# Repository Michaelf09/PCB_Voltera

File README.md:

# Tiltis Key - PCB KiCad

Projet KiCad réalisé dans le cadre du projet PI² de l’ESILV.
Conception du PCB de la Tiltis Key avec fabrication prévue sur imprimante Voltera.

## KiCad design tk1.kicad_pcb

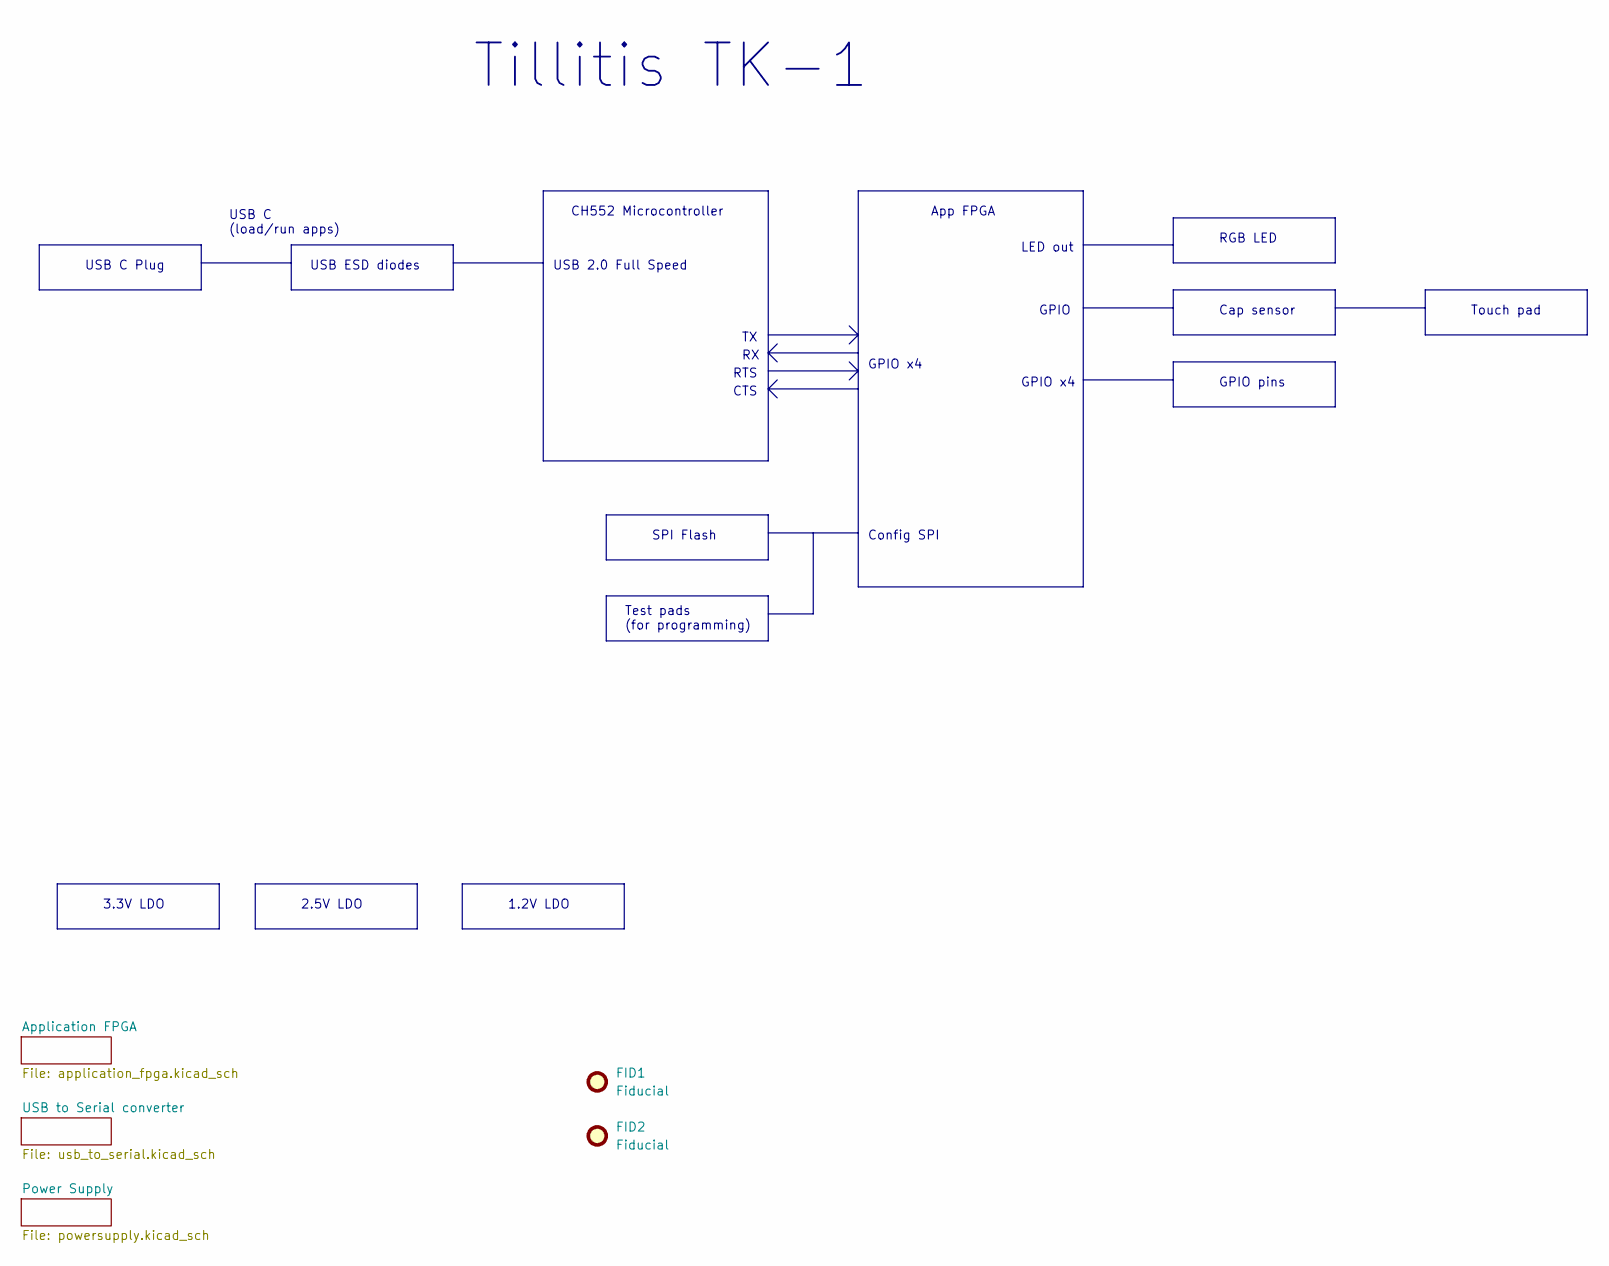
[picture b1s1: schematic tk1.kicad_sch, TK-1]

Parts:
FID1, FID2: Fiducial; Fiducial_0.75mm_Mask1.5mm

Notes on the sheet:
USB ESD diodes
Touch pad
GPIO x4
GPIO pins
Cap sensor
USB 2.0 Full Speed
RTS
USB C Plug
CH552 Microcontroller
RGB LED
USB C (load/run apps)
1.2V LDO
3.3V LDO
CTS
2.5V LDO
App FPGA
Config SPI
Tillitis TK-1
SPI Flash
GPIO
LED out
Test pads (for programming)

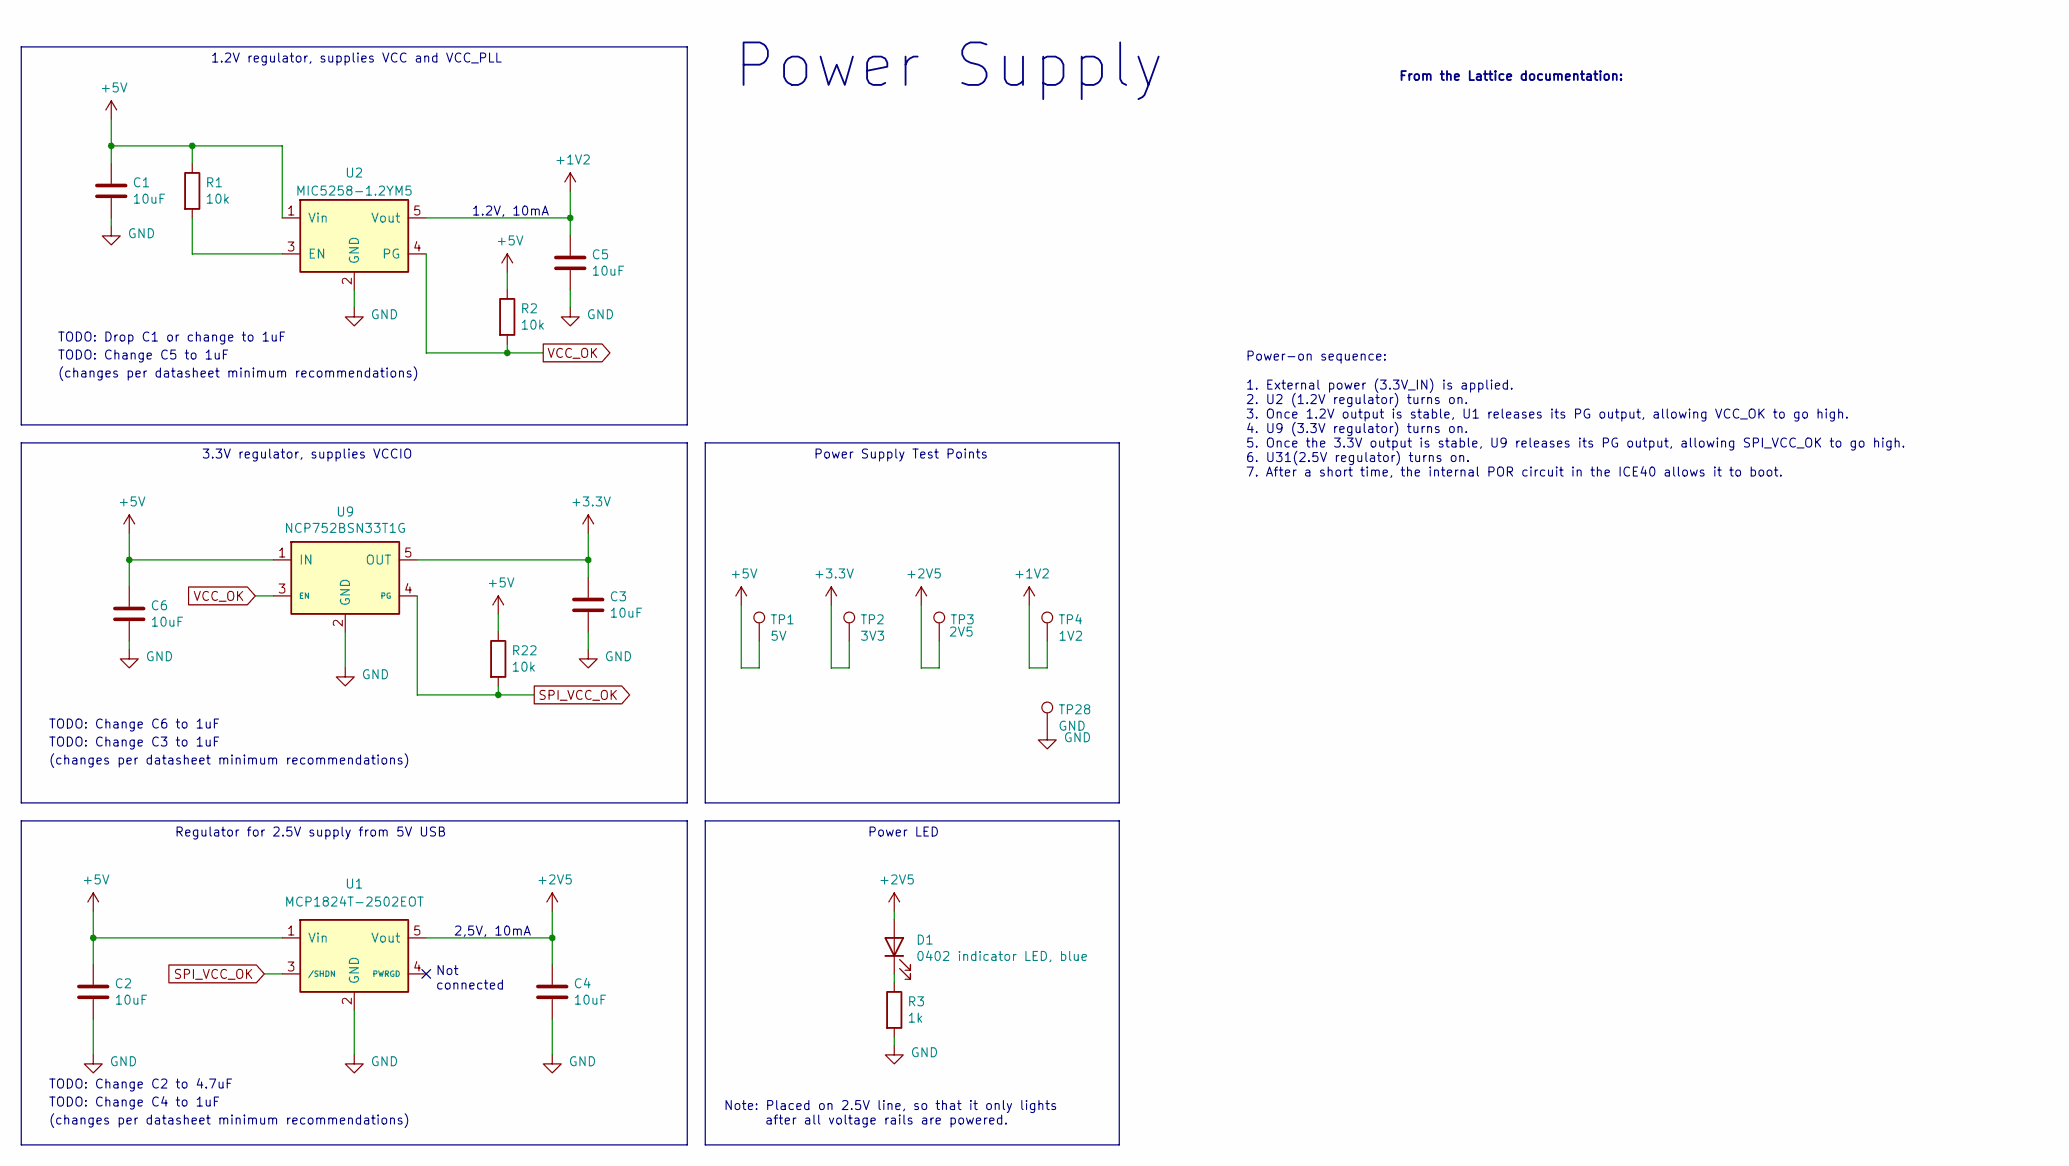
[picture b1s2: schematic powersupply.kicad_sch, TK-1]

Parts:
C1, C2, C3, C4, C5, C6: 10uF; C_0805_2012Metric
D1: 0402 indicator LED, blue; LED_0805_2012Metric; Manufacturer Part Number NCD0402B1
R1, R2, R22: 10k; R_0805_2012Metric
R3: 1k; R_0805_2012Metric
TP1: 5V; TestPoint_Pad_D1.0mm
TP2: 3V3; TestPoint_Pad_D1.0mm
TP3: 2V5; TestPoint_Pad_D1.0mm
TP4: 1V2; TestPoint_Pad_D1.0mm
TP28: GND; TestPoint_Pad_D1.0mm
U1: MCP1824T-2502EOT; SOT-23-5; Manufacturer Part Number MCP1824T-2502EOT
U2: MIC5258-1.2YM5; SOT-23-5; Manufacturer Part Number MIC5258-1.2YM5
U9: NCP752BSN33T1G; Manufacturer Part Number NCP752BSN33T1G

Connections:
+1V2: C5.1, TP4.1, U2.5 (Vout); also elsewhere on the board
+2V5: C4.1, D1.2 (A), TP3.1, U1.5 (Vout); also elsewhere on the board
+3.3V: C3.1, TP2.1, U9.5 (OUT); also elsewhere on the board
+5V: C1.1, C2.1, C6.1, R1.1, R2.1, R22.1, TP1.1, U1.1 (Vin), U2.1 (Vin), U9.1 (IN); also elsewhere on the board
GND: C1.2, C2.2, C3.2, C4.2, C5.2, C6.2, R3.2, TP28.1, U1.2 (GND), U2.2 (GND), U9.2 (GND); also elsewhere on the board
unnamed: D1.1 (K), R3.1
unnamed: R1.2, U2.3 (EN)
SPI_VCC_OK: R22.2, U1.3 (/SHDN), U9.4 (PG)
VCC_OK: R2.2, U2.4 (PG), U9.3 (EN)

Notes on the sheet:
Power-on sequence: 1. External power (3.3V_IN) is applied. 2. U2 (1.2V regulator) turns on. 3. Once 1.2V output is stable, U1 releases its PG output, allowing VCC_OK to go high. 4. U9 (3.3V regulator) turns on. 5. Once the 3.3V output is stable, U9 releases its PG output, allowing SPI_VCC_OK to go 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
TODO: Change C2 to 4.7uF
(changes per datasheet minimum recommendations)
TODO: Change C6 to 1uF
2,5V, 10mA
Note: Placed on 2.5V line, so that it only lights after all voltage rails are powered.
TODO: Change C3 to 1uF
1.2V, 10mA
Power Supply
TODO: Drop C1 or change to 1uF
TODO: Change C5 to 1uF
From the Lattice documentation:
1.2V regulator, supplies VCC and VCC_PLL
3.3V regulator, supplies VCCIO
TODO: Change C4 to 1uF
Not connected
Power Supply Test Points
Power LED
Regulator for 2.5V supply from 5V USB

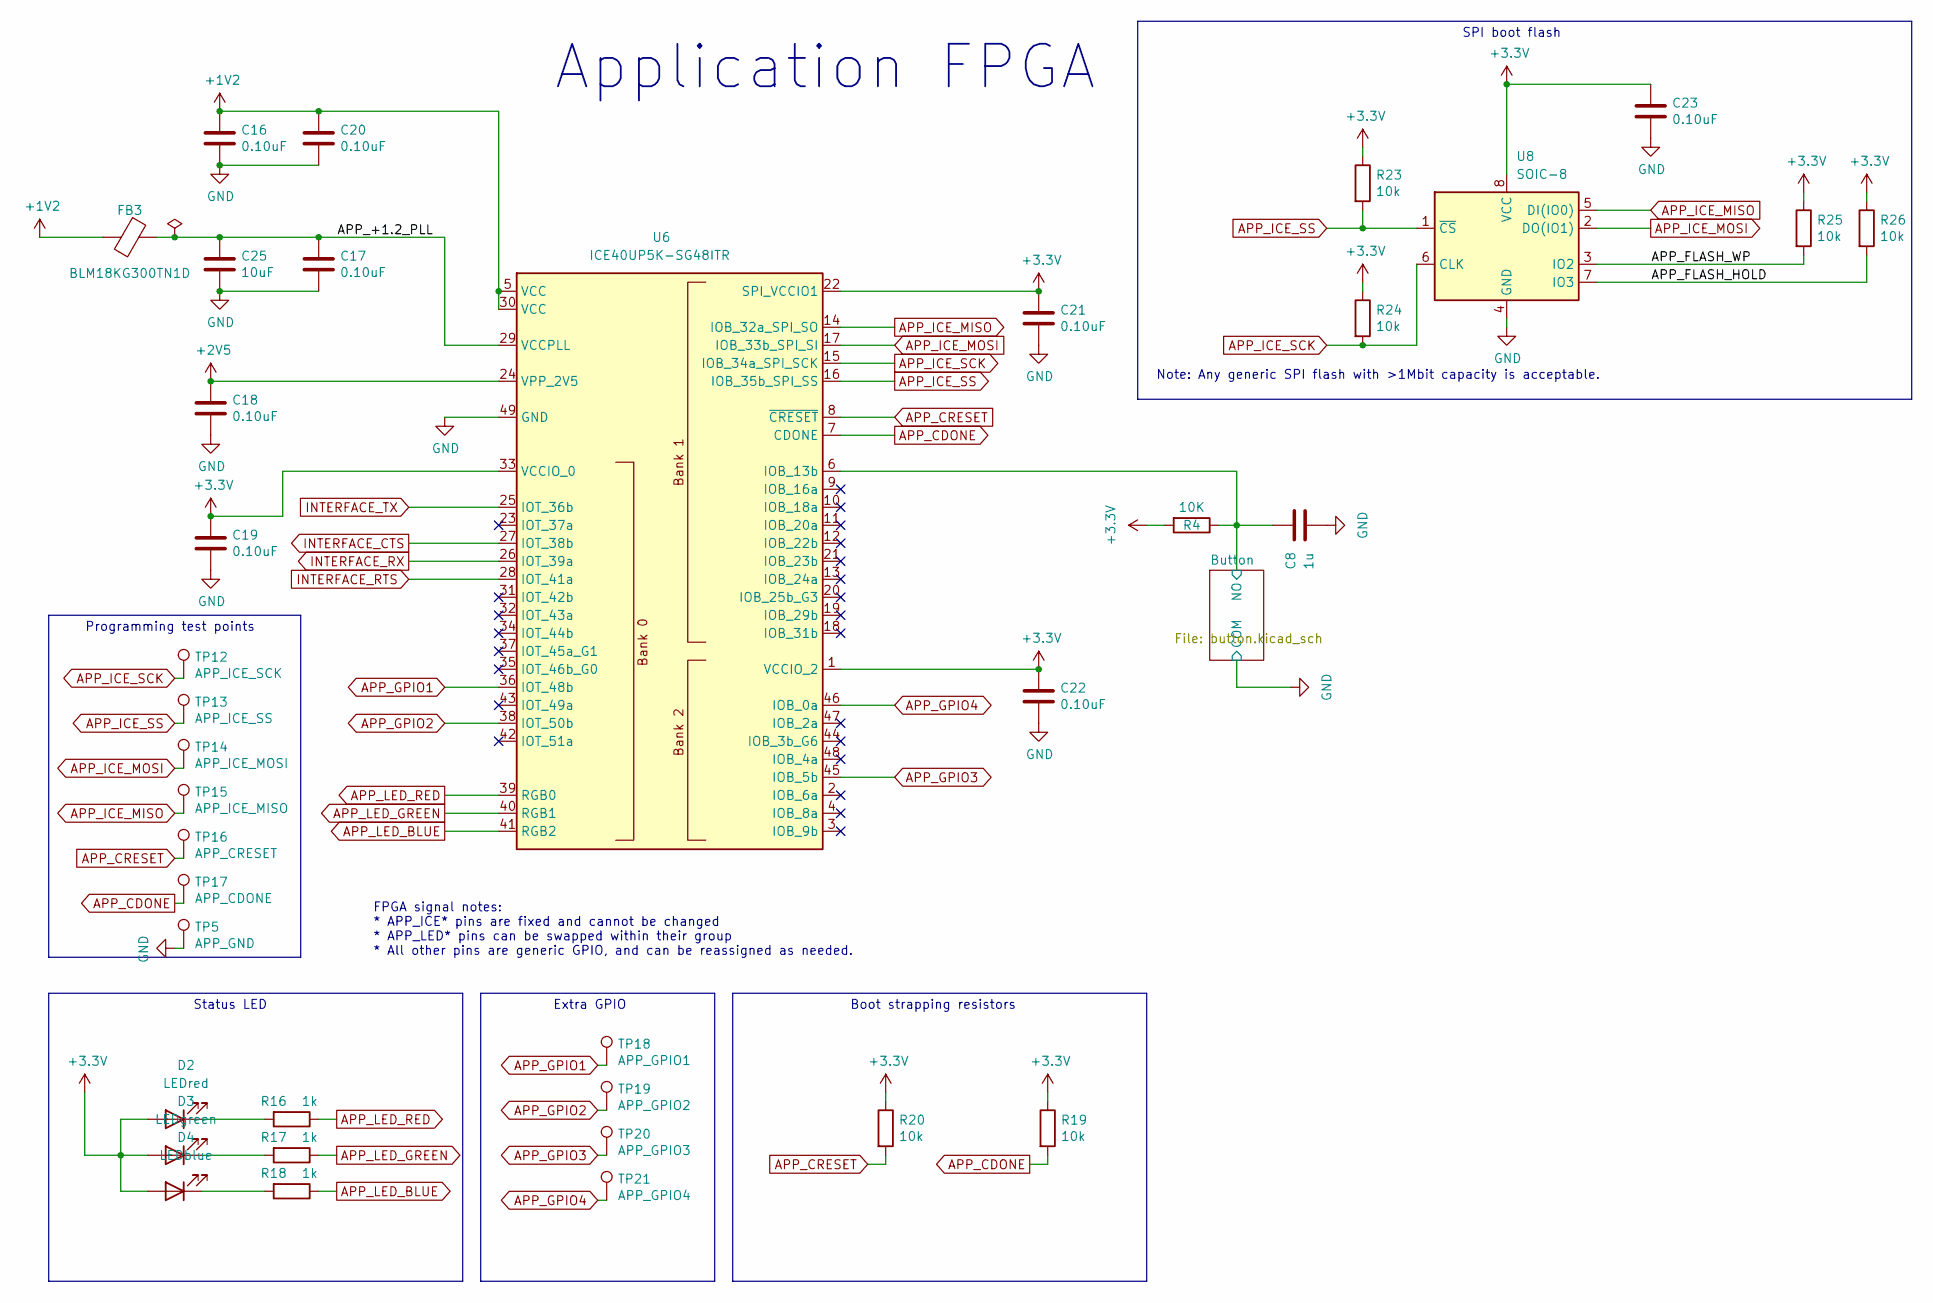
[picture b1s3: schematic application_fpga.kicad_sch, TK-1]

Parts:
C8: 1u; C_0805_2012Metric_Pad1.18x1.45mm_HandSolder
C16, C17, C18, C19, C20, C21, C22, C23: 0.10uF; C_0805_2012Metric
C25: 10uF; C_0805_2012Metric
D2: LEDred; LED_0805_2012Metric_Pad1.15x1.40mm_HandSolder
D3: LEDgreen; LED_0805_2012Metric_Pad1.15x1.40mm_HandSolder
D4: LEDblue; LED_0805_2012Metric_Pad1.15x1.40mm_HandSolder
FB3: BLM18KG300TN1D; Ferritbead_0603_1608Metric; Manufacturer Part Number BLM18KG300TN1D
R4: 10K; R_0805_2012Metric_Pad1.20x1.40mm_HandSolder
R16, R17, R18: 1k; R_0805_2012Metric
R19, R20, R23, R24, R25, R26: 10k; R_0805_2012Metric
TP5: APP_GND; TestPoint_Pad_D1.0mm
TP12: APP_ICE_SCK; TestPoint_Pad_D1.0mm
TP13: APP_ICE_SS; TestPoint_Pad_D1.0mm
TP14: APP_ICE_MOSI; TestPoint_Pad_D1.0mm
TP15: APP_ICE_MISO; TestPoint_Pad_D1.0mm
TP16: APP_CRESET; TestPoint_Pad_D1.0mm
TP17: APP_CDONE; TestPoint_Pad_D1.0mm
TP18: APP_GPIO1; TestPoint_Pad_D1.0mm
TP19: APP_GPIO2; TestPoint_Pad_D1.0mm
TP20: APP_GPIO3; TestPoint_Pad_D1.0mm
TP21: APP_GPIO4; TestPoint_Pad_D1.0mm
U6: ICE40UP5K-SG48ITR; QFN-48-1EP_7x7mm_P0.5mm_EP5.6x5.6mm; Manufacturer Part Number ICE40UP5K-SG48ITR
U8: SOIC-8; SOIC-8_3.9x4.9mm_P1.27mm; Manufacturer Part Number W25Q80DVUXIE

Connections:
+1V2: C16.1, C20.1, FB3.2, U6.5 (VCC), U6.30 (VCC); also elsewhere on the board
+2V5: C18.1, U6.24 (VPP_2V5); also elsewhere on the board
+3.3V: C19.1, C21.1, C22.1, C23.1, D2.2 (A), D3.2 (A), D4.2 (A), R4.2, R19.1, R20.1, R23.1, R24.1, R25.1, R26.1, U6.1 (VCCIO_2), U6.22 (SPI_VCCIO1), U6.33 (VCCIO_0), U8.8 (VCC); also elsewhere on the board
/Application FPGA/APP_+1.2_PLL: C17.1, C25.1, FB3.1, U6.29 (VCCPLL)
/Application FPGA/APP_FLASH_HOLD: R26.2, U8.7 (IO3)
/Application FPGA/APP_FLASH_WP: R25.2, U8.3 (IO2)
/Application FPGA/Button/NO: C8.1, R4.1, U6.6 (IOB_13b); also elsewhere on the board
APP_CDONE: R19.2, TP17.1, U6.7 (CDONE)
APP_CRESET: R20.2, TP16.1, U6.8 (~CRESET)
APP_GPIO1: TP18.1, U6.36 (IOT_48b)
APP_GPIO2: TP19.1, U6.38 (IOT_50b)
APP_GPIO3: TP20.1, U6.45 (IOB_5b)
APP_GPIO4: TP21.1, U6.46 (IOB_0a)
APP_ICE_MISO: TP15.1, U6.14 (IOB_32a_SPI_SO), U8.5 (DI(IO0))
APP_ICE_MOSI: TP14.1, U6.17 (IOB_33b_SPI_SI), U8.2 (DO(IO1))
APP_ICE_SCK: R24.2, TP12.1, U6.15 (IOB_34a_SPI_SCK), U8.6 (CLK)
APP_ICE_SS: R23.2, TP13.1, U6.16 (IOB_35b_SPI_SS), U8.1 (~CS)
APP_LED_BLUE: R18.1, U6.41 (RGB2)
APP_LED_GREEN: R17.1, U6.40 (RGB1)
APP_LED_RED: R16.1, U6.39 (RGB0)
GND: C8.2, C16.2, C17.2, C18.2, C19.2, C20.2, C21.2, C22.2, C23.2, C25.2, TP5.1, U6.49 (GND), U8.4 (GND); also elsewhere on the board
INTERFACE_CTS: U6.27 (IOT_38b); also elsewhere on the board
INTERFACE_RTS: U6.28 (IOT_41a); also elsewhere on the board
INTERFACE_RX: U6.26 (IOT_39a); also elsewhere on the board
INTERFACE_TX: U6.25 (IOT_36b); also elsewhere on the board
unnamed: D2.1 (K), R16.2
unnamed: D3.1 (K), R17.2
unnamed: D4.1 (K), R18.2

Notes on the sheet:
Application FPGA
SPI boot flash
FPGA signal notes: * APP_ICE* pins are fixed and cannot be changed * APP_LED* pins can be swapped within their group * All other pins are generic GPIO, and can be reassigned as needed.
Boot strapping resistors
Status LED
Programming test points
Note: Any generic SPI flash with >1Mbit capacity is acceptable.
Extra GPIO

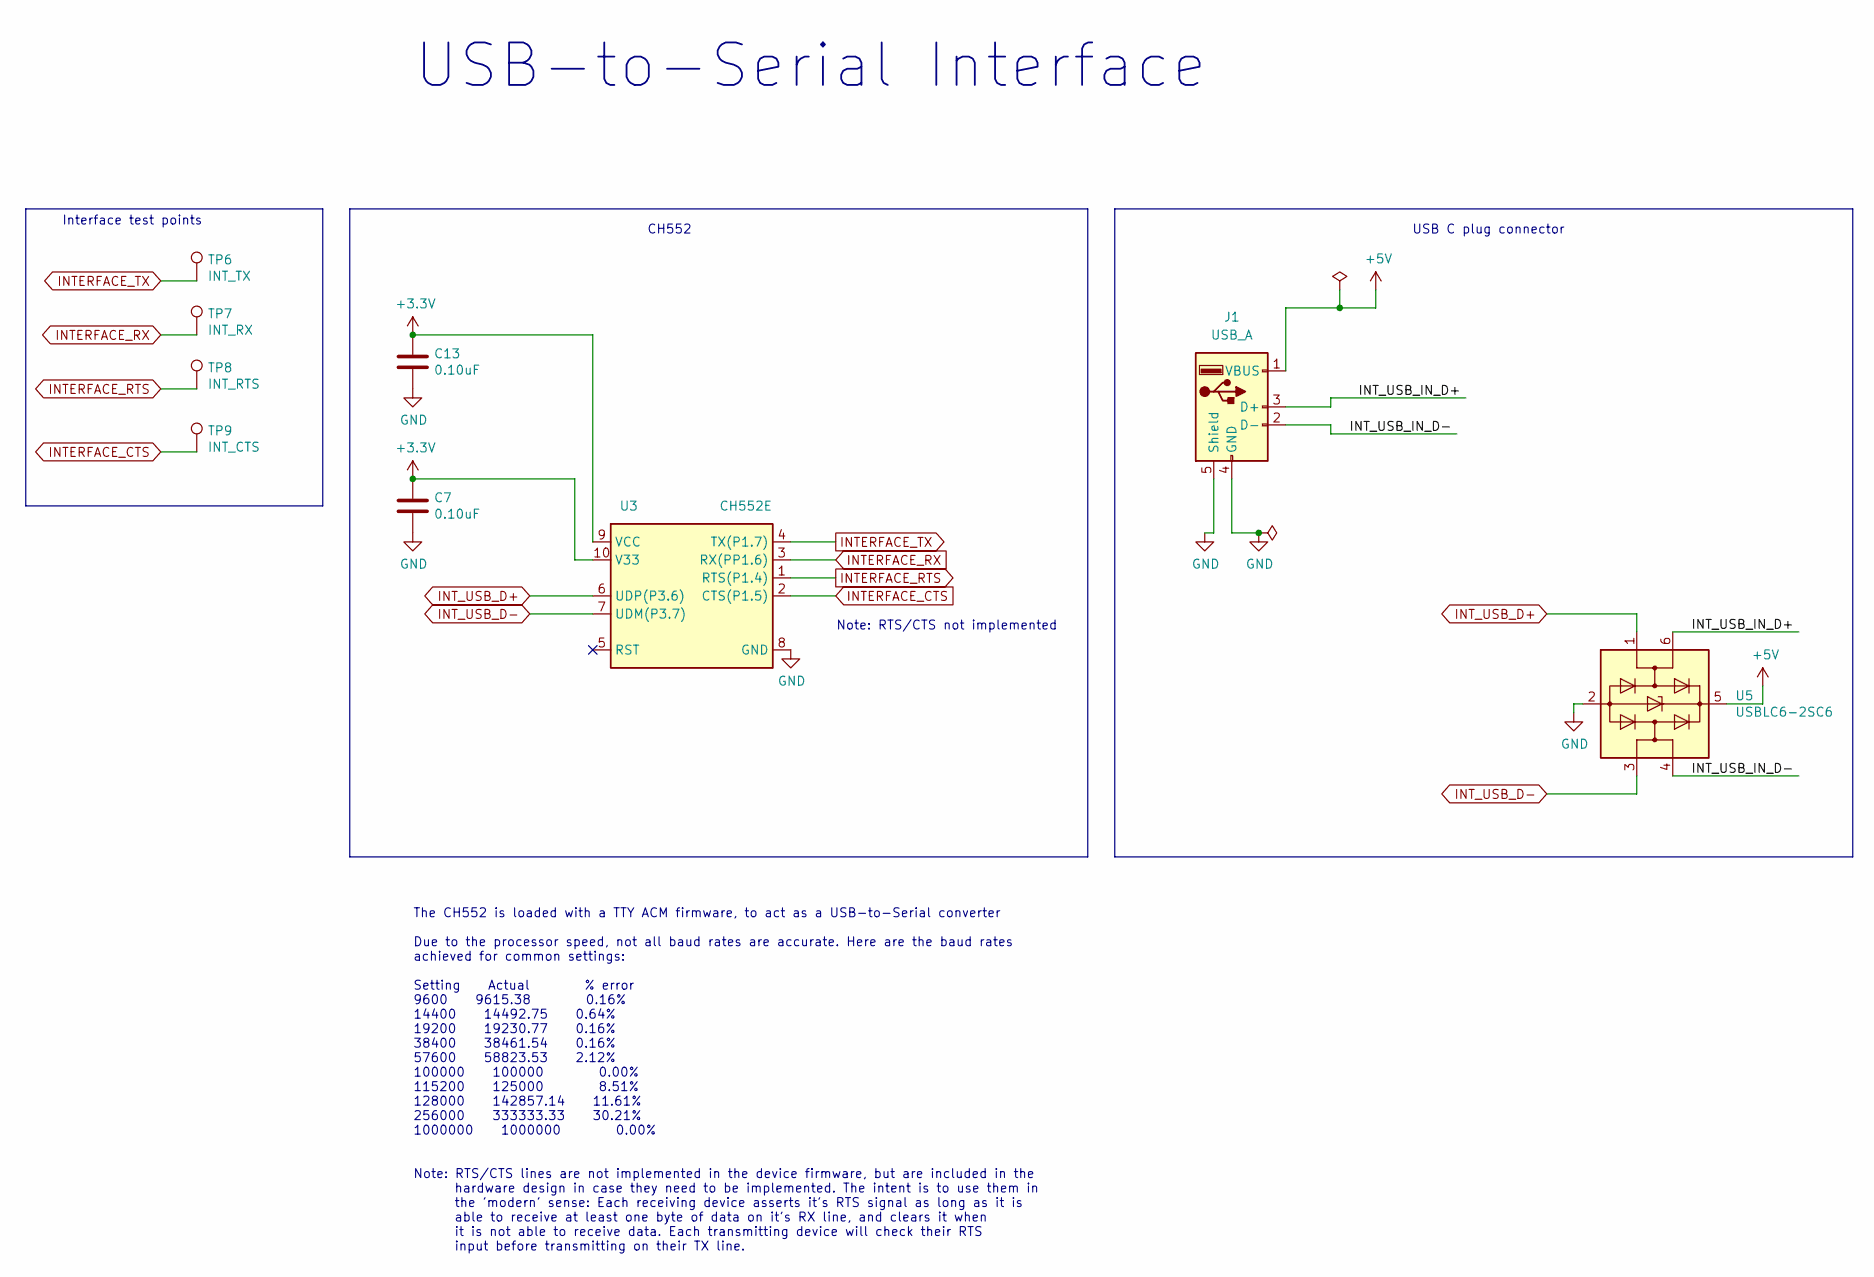
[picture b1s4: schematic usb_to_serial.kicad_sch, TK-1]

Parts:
C7, C13: 0.10uF; C_0805_2012Metric
J1: USB_A; USB_A_Kycon_KUSBX-AS1N-B_Horizontal
TP6: INT_TX; TestPoint_Pad_D1.0mm
TP7: INT_RX; TestPoint_Pad_D1.0mm
TP8: INT_RTS; TestPoint_Pad_D1.0mm
TP9: INT_CTS; TestPoint_Pad_D1.0mm
U3: CH552E; MSOP-10_3x3mm_P0.5mm; Manufacturer Part Number CH552E
U5: USBLC6-2SC6; SOT-23-6; Manufacturer Part Number USBLC6-2SC6

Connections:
+3.3V: C7.1, C13.1, U3.9 (VCC), U3.10 (V33); also elsewhere on the board
+5V: J1.1 (VBUS), U5.5 (VBUS); also elsewhere on the board
/USB to Serial converter/INT_USB_IN_D+: J1.3 (D+), U5.6 (I/O1)
/USB to Serial converter/INT_USB_IN_D-: J1.2 (D-), U5.4 (I/O2)
GND: C7.2, C13.2, J1.4 (GND), J1.5 (Shield), U3.8 (GND), U5.2 (GND); also elsewhere on the board
INTERFACE_CTS: TP9.1, U3.2 (CTS(P1.5)); also elsewhere on the board
INTERFACE_RTS: TP8.1, U3.1 (RTS(P1.4)); also elsewhere on the board
INTERFACE_RX: TP7.1, U3.3 (RX(PP1.6)); also elsewhere on the board
INTERFACE_TX: TP6.1, U3.4 (TX(P1.7)); also elsewhere on the board
INT_USB_D+: U3.6 (UDP(P3.6)), U5.1 (I/O1)
INT_USB_D-: U3.7 (UDM(P3.7)), U5.3 (I/O2)

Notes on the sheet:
USB C plug connector
CH552
USB-to-Serial Interface
The CH552 is loaded with a TTY ACM firmware, to act as a USB-to-Serial converter Due to the processor speed, not all baud rates are accurate. Here are the baud rates achieved for common settings: Setting Actual % error 9600 9615.38 0.16% 14400 14492.75 0.64% 19200 19230.77 0.16% 38400 38461.54 0.16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
Interface test points
Note: RTS/CTS not implemented

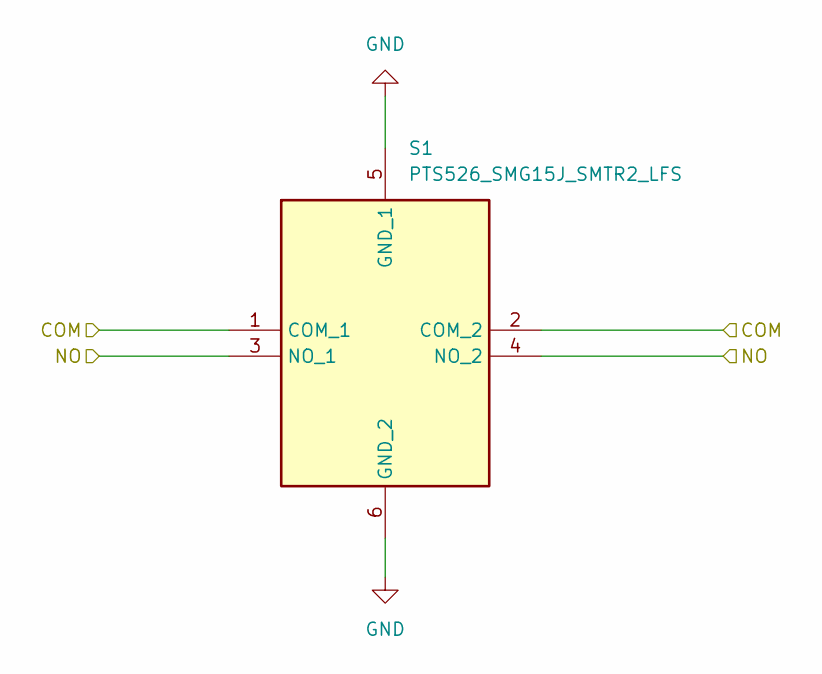
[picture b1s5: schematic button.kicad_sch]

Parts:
S1: PTS526_SMG15J_SMTR2_LFS; PTS526SMG15JSMTR2LFS; Manufacturer_Part_Number PTS526 SMG15J SMTR2 LFS; Mouser Part Number 611-TS526SMG15JSMR2L

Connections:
/Application FPGA/Button/NO: S1.3 (NO_1), S1.4 (NO_2); also elsewhere on the board
GND: S1.1 (COM_1), S1.2 (COM_2), S1.5 (GND_1), S1.6 (GND_2); also elsewhere on the board

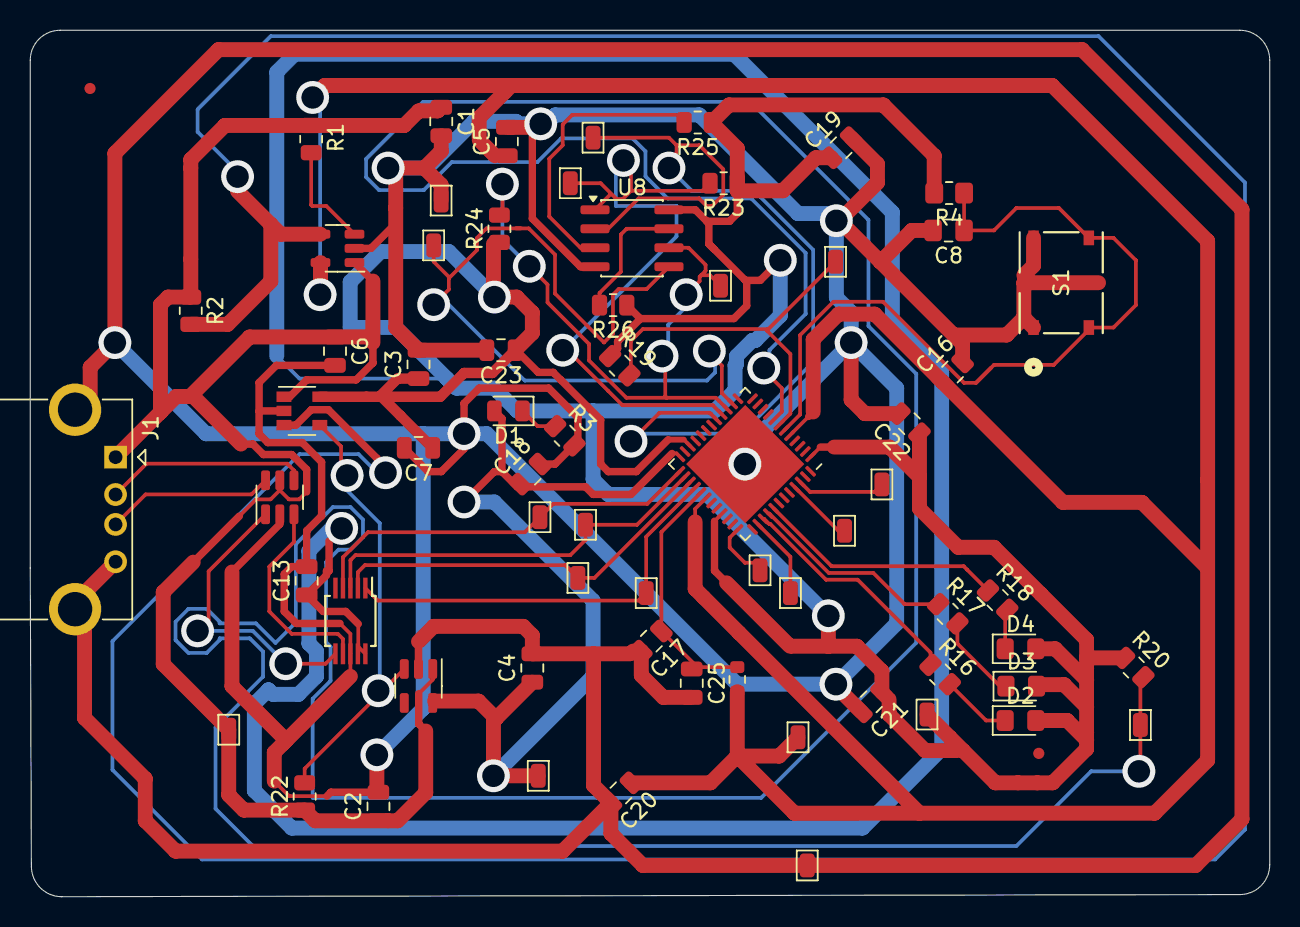
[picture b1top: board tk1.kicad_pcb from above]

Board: 2 copper layers, 83.0 x 58.0 mm, 68 parts (0 on the bottom side), 37 nets.

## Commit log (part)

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2026-03-02 Add README for Tiltis Key PCB
    Added project description and purpose for Tiltis Key PCB.
2026-03-17 Correction condensateur en trop + PCB correspondant au schéma
2026-03-17 Ajout bouton du même style que les projets du LabCyber
